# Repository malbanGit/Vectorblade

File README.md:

# Vectorblade

These are all sources and ressources for "Vectorblade" a Vectrex game and port of the good old "Deluxe Galaga" / "Warblade".

To build it you <b>need</b> Vide, since the game consists of four seperated banks and address information "over" banks is injected into each 
bank-binary by Vide in an additional "linker" stage.

Vide is a VECTREX INTEGRATED DEVELOPMENT ENVIRONMENT (http://vide.malban.de), it is free and can be downloaded for several OS at the given homepage.

More information about this repository, all files contained within and copyright status can be found at: 

http://vide.malban.de/vectorblade

Also look in the "menu" of the Vectorblade item.

Concerning the coding of Vectorblade and the source structure, look especially at:

http://vide.malban.de/vectorblade/building-vectorblade

Thank you!

Malban

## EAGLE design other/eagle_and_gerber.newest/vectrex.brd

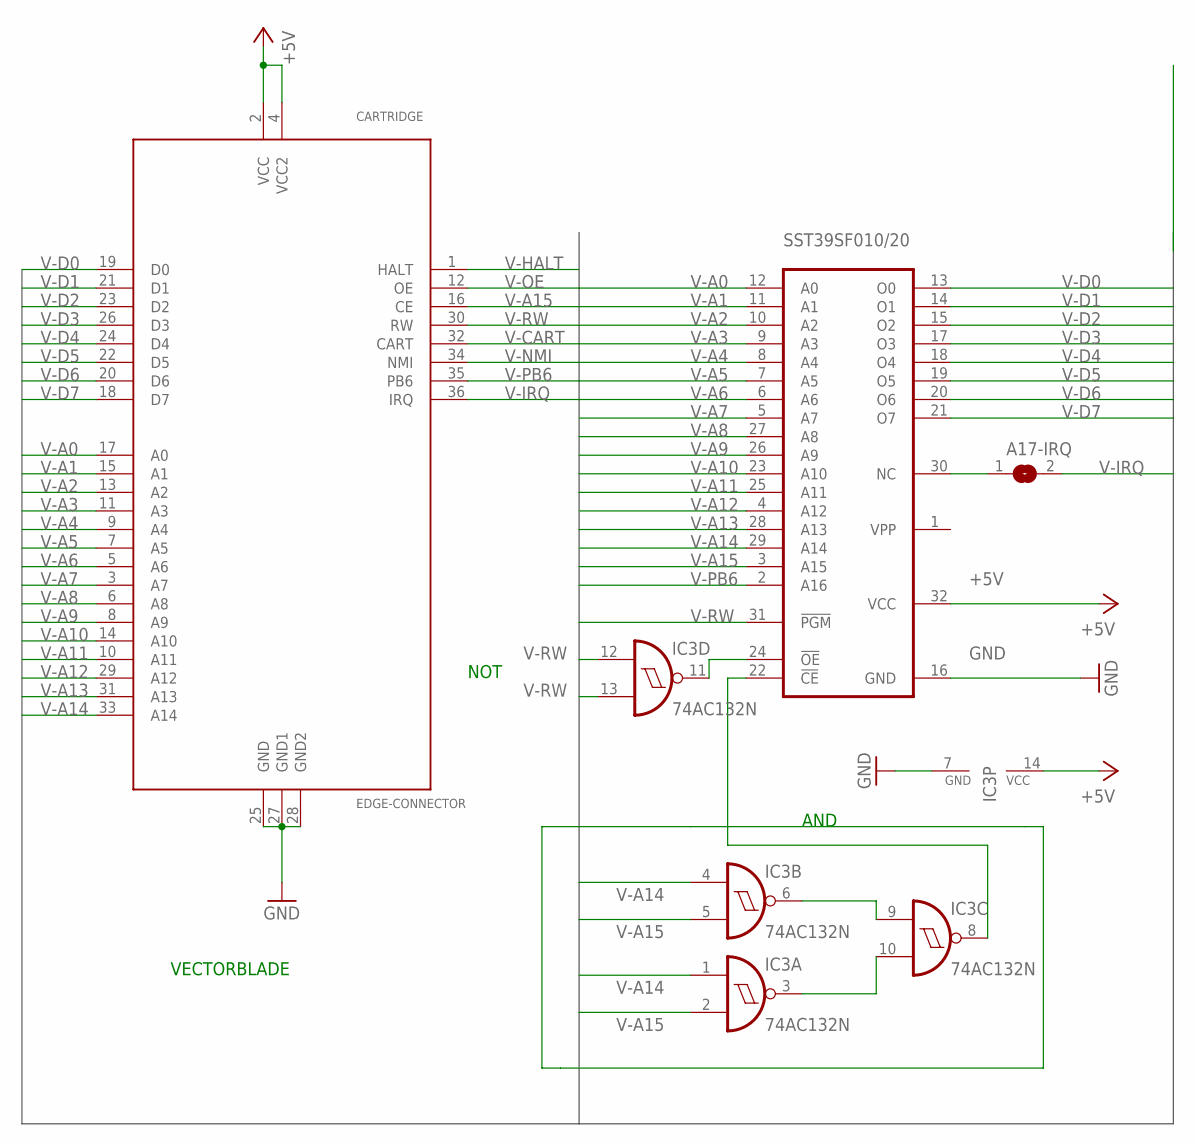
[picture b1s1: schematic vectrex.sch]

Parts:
A17-IRQ: SJ
CARTRIDGE: EDGE-CONNECTOR
IC3: 74AC132N; DIL14
SST39SF010/20: 27C1001A; DIL32

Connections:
+5V: CARTRIDGE.2 (VCC), CARTRIDGE.4 (VCC2), IC3.14 (VCC), SST39SF010/20.32 (VCC)
GND: CARTRIDGE.25 (GND), CARTRIDGE.27 (GND1), CARTRIDGE.28 (GND2), IC3.7 (GND), SST39SF010/20.16 (GND)
unnamed: IC3.8 (O), SST39SF010/20.22 (!CE)
unnamed: IC3.6 (O), IC3.9 (I0)
unnamed: IC3.3 (O), IC3.10 (I1)
unnamed: IC3.11 (O), SST39SF010/20.24 (!OE)
unnamed: A17-IRQ.1, SST39SF010/20.30 (NC)
V-A0: CARTRIDGE.17 (A0), SST39SF010/20.12 (A0)
V-A1: CARTRIDGE.15 (A1), SST39SF010/20.11 (A1)
V-A2: CARTRIDGE.13 (A2), SST39SF010/20.10 (A2)
V-A3: CARTRIDGE.11 (A3), SST39SF010/20.9 (A3)
V-A4: CARTRIDGE.9 (A4), SST39SF010/20.8 (A4)
V-A5: CARTRIDGE.7 (A5), SST39SF010/20.7 (A5)
V-A6: CARTRIDGE.5 (A6), SST39SF010/20.6 (A6)
V-A7: CARTRIDGE.3 (A7), SST39SF010/20.5 (A7)
V-A8: CARTRIDGE.6 (A8), SST39SF010/20.27 (A8)
V-A9: CARTRIDGE.8 (A9), SST39SF010/20.26 (A9)
V-A10: CARTRIDGE.14 (A10), SST39SF010/20.23 (A10)
V-A11: CARTRIDGE.10 (A11), SST39SF010/20.25 (A11)
V-A12: CARTRIDGE.29 (A12), SST39SF010/20.4 (A12)
V-A13: CARTRIDGE.31 (A13), SST39SF010/20.28 (A13)
V-A14: CARTRIDGE.33 (A14), IC3.1 (I0), IC3.4 (I0), SST39SF010/20.29 (A14)
V-A15: CARTRIDGE.16 (CE), IC3.2 (I1), IC3.5 (I1), SST39SF010/20.3 (A15)
V-CART: CARTRIDGE.32 (CART)
V-D0: CARTRIDGE.19 (D0), SST39SF010/20.13 (O0)
V-D1: CARTRIDGE.21 (D1), SST39SF010/20.14 (O1)
V-D2: CARTRIDGE.23 (D2), SST39SF010/20.15 (O2)
V-D3: CARTRIDGE.26 (D3), SST39SF010/20.17 (O3)
V-D4: CARTRIDGE.24 (D4), SST39SF010/20.18 (O4)
V-D5: CARTRIDGE.22 (D5), SST39SF010/20.19 (O5)
V-D6: CARTRIDGE.20 (D6), SST39SF010/20.20 (O6)
V-D7: CARTRIDGE.18 (D7), SST39SF010/20.21 (O7)
V-HALT: CARTRIDGE.1 (HALT)
V-IRQ: A17-IRQ.2, CARTRIDGE.36 (IRQ)
V-NMI: CARTRIDGE.34 (NMI)
V-OE: CARTRIDGE.12 (OE)
V-PB6: CARTRIDGE.35 (PB6), SST39SF010/20.2 (A16)
V-RW: CARTRIDGE.30 (RW), IC3.12 (I0), IC3.13 (I1), SST39SF010/20.31 (!PGM)

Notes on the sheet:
VECTORBLADE
AND
NOT

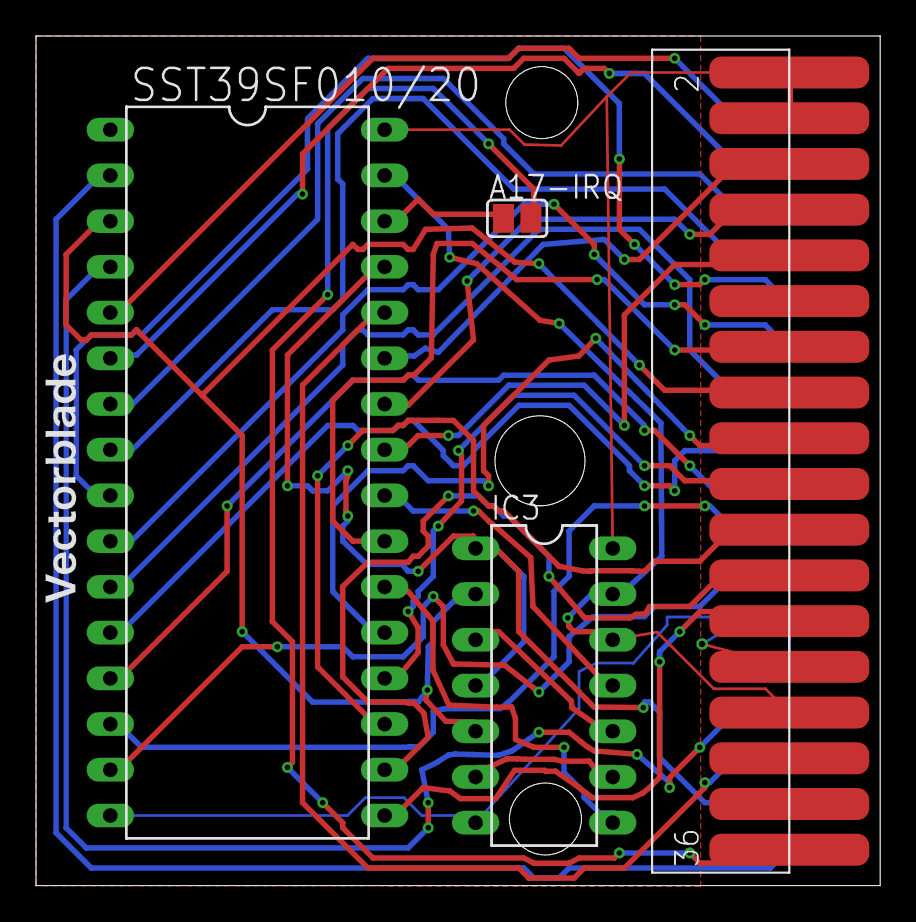
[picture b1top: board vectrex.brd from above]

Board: 2 copper layers, 46.9 x 47.2 mm, 4 parts (0 on the bottom side), 34 nets.

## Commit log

2020-09-30 Vectorblade version 1.03
2020-09-30 deleted old binaries
2020-10-04 Update commonGround.i
    Changed compile version number to 1.04 - the debounce fix!
2020-11-10 Update commonGround.i
    Brett:
    added a tiny bit of delay in the FLASH write routine, and game save RAM read routine
    to allow fast low capacitance AND gates used on the cartridge to still function correctly.
2020-11-10 Update flashSupport.asm
    Brett:
    added a tiny bit of delay in the FLASH write routine, and game save RAM read routine
    to allow fast low capacitance AND gates used on the cartridge to still function correctly.
2020-11-10 Update mainBank0.asm
    Brett:
    added a tiny bit of delay in the FLASH write routine, and game save RAM read routine
    to allow fast low capacitance AND gates used on the cartridge to still function correctly.
2020-12-26 Update macro.i
    V1.06: Intensity macros changed.
2020-12-26 Update commonGround.i
    V1.06: Intensity macros changed.
2020-12-26 Update desktop.asm
    V1.06: Intensity macros changed.
2021-01-08 alle changes for V1.07
2021-01-10 changes to V1.08
2021-01-10 changes to V1.09
2021-02-19 changes to V1.10
2021-02-25 Update flashSupport.asm
    Fixed Bug discovered by Ralf Kornmann:
    As some of you might know VectorBlade is using only one memory chip. Therefore all the settings and high scores will be saved on the same chip that already contains the game itself. While the memory 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
2021-02-25 Update commonGround.i
    Fixed Bug discovered by Ralf Kornmann:
    As some of you might know VectorBlade is using only one memory chip. Therefore all the settings and high scores will be saved on the same chip that already contains the game itself. While the memory 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
2021-02-25 Delete VectorbladeV1.10.bin
    removed possible corrupting bin file Version 1.10
2021-02-25 changes to V1.11
2021-06-21 changes to V1.12
2021-08-02 changes to V1.13
